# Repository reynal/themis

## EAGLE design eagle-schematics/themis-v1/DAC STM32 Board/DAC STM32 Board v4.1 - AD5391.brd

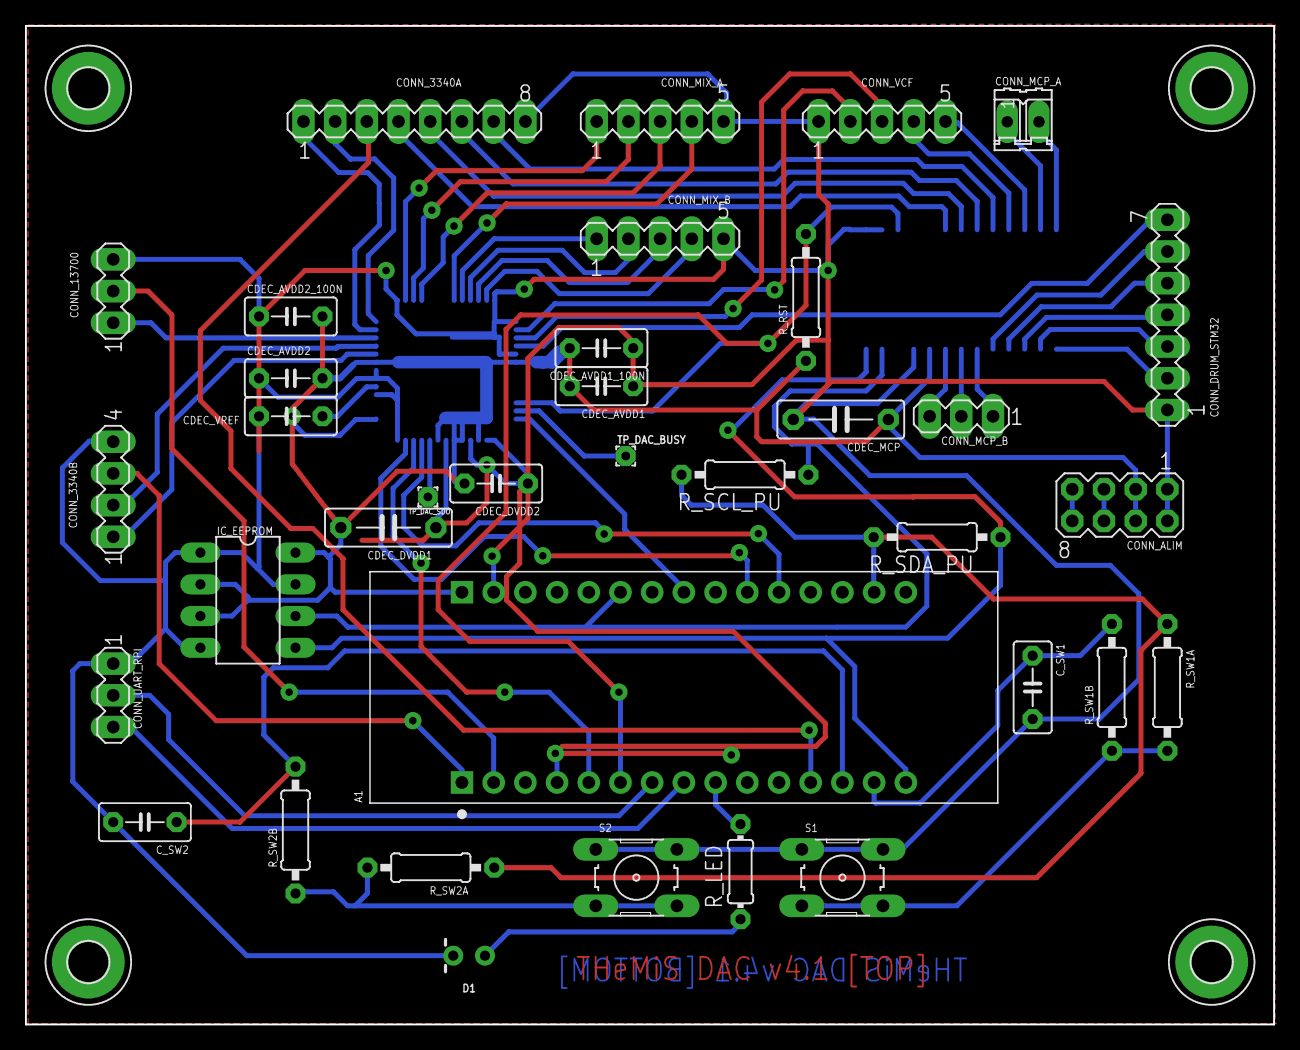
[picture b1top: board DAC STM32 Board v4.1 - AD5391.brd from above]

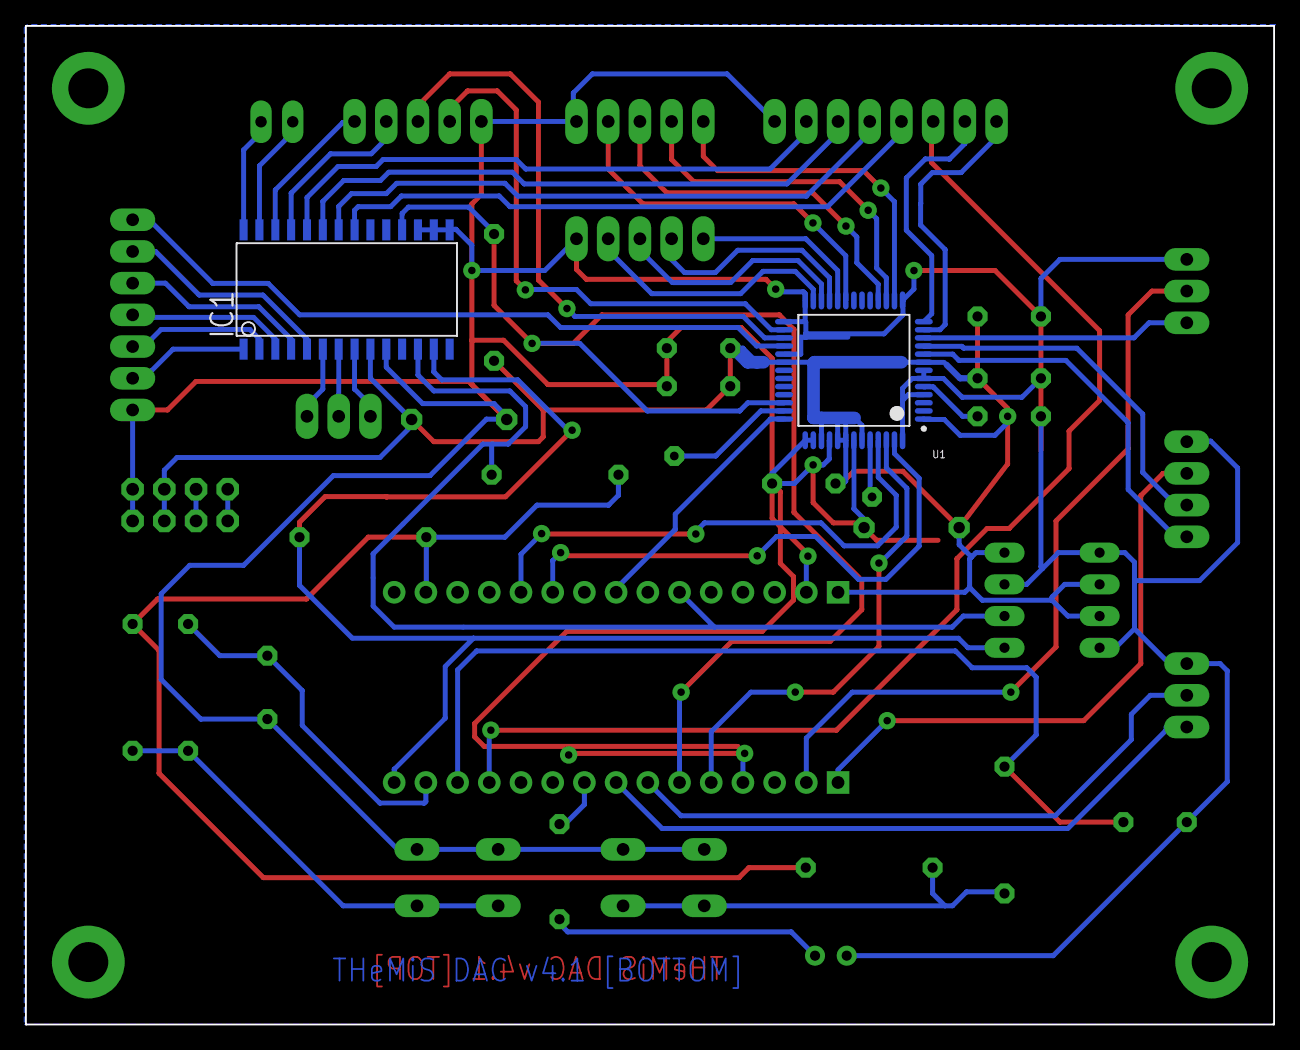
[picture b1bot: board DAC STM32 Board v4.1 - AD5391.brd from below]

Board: 2 copper layers, 100.0 x 80.0 mm, 42 parts (2 on the bottom side), 58 nets.

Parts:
A1: NUCLEO-F303K8; MODULE_NUCLEO-F303K8
CDEC_AVDD1, CDEC_AVDD2: 10u; C050-030X075
CDEC_AVDD1_100N, CDEC_AVDD2_100N: 100n; C050-030X075
CDEC_DVDD1: 100n; C075-032X103
CDEC_DVDD2: 100n; C050-030X075
CDEC_MCP: 100n; C075-032X103
CDEC_VREF: 100n; C050-030X075
CONN_3340A: MA08-1
CONN_3340B: MA04-1
CONN_13700: MA03-1
CONN_ALIM: MA04-2
CONN_DRUM_STM32: MA07-1
CONN_MCP_A: 02P
CONN_MCP_B: MA03-1
CONN_MIX_A: MA05-1
CONN_MIX_B: MA05-1
CONN_UART_RPI: MA03-1
CONN_VCF: MA05-1
C_SW1, C_SW2: 100n; C050-030X075
D1: LED_3MM-NS
H1, H2, H3, H4: MOUNT-PAD-ROUND3.2; 3,2-PAD
IC1: MCP23017SO; SO28W
IC_EEPROM: 24C04AP; DIL8
R_LED: 330; 0204/7
R_RST: 10k; 0207/10
R_SCL_PU: 1k; 0207/10
R_SDA_PU: 1k; 0207/10
R_SW1A, R_SW1B, R_SW2A, R_SW2B: 10k; 0207/10
S1, S2: B3F-10XX
TP_DAC_BUSY: PAD-TESTPOINT; 1,6/0,8
TP_DAC_SDO: PAD-TESTPOINT; 1,6/0,8
U1: ANALOG_DEVICES_AD5391BSTZ-3ANALOG_DEVICES_AD5391B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; ANALOG_DEVICES_AD5391BSTZ-3_0

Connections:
3V3: A1.4.14, R_SCL_PU.2, R_SDA_PU.2, R_SW1A.1, R_SW2A.1
5V: A1.4.1, CDEC_AVDD1.2, CDEC_AVDD1_100N.2, CDEC_AVDD2.2, CDEC_AVDD2_100N.2, CDEC_DVDD1.2, CDEC_DVDD2.2, CDEC_MCP.1, CONN_ALIM.3, CONN_ALIM.4, IC1.9, IC_EEPROM.2, IC_EEPROM.3, IC_EEPROM.8, R_RST.1, U1.1, U1.8, U1.32, U1.42, U1.44, U1.45, U1.47
15V: CONN_ALIM.7, CONN_ALIM.8
411_IN_PULSE: CONN_3340A.4, IC1.21
411_IN_SAW: CONN_3340A.7, IC1.24
411_IN_SYNC: CONN_3340A.6, IC1.23
411_IN_TRI: CONN_3340A.5, IC1.22
-15V: CONN_ALIM.5, CONN_ALIM.6
CALIB_3340A: A1.3.12, CONN_3340A.3
CALIB_3340B: A1.3.1, CONN_3340B.3
CALIB_13700: A1.3.2, CONN_13700.2
CV_CUTOFF: CONN_VCF.2, U1.28
CV_FREQ_3340A: CONN_3340A.1, U1.12
CV_FREQ_3340B: CONN_3340B.1, U1.9
CV_FREQ_13700: CONN_13700.1, U1.11
CV_PWM_3340A: CONN_3340A.2, U1.13
CV_PWM_3340B: CONN_3340B.2, U1.10
CV_RES: CONN_VCF.3, U1.29
DAC_LDAC: A1.4.8, U1.39
DAC_SYNC: A1.4.10, U1.51
DRUM_BD: CONN_DRUM_STM32.2, IC1.1
DRUM_RIM: CONN_DRUM_STM32.4, IC1.3
DRUM_SNARE: CONN_DRUM_STM32.3, IC1.2
DRUM_TOM1: CONN_DRUM_STM32.5, IC1.4
DRUM_TOM2: CONN_DRUM_STM32.6, IC1.5
GAIN1_A: CONN_MIX_A.3, U1.17
GAIN1_B: CONN_MIX_B.3, U1.24
GAIN2_A: CONN_MIX_A.4, U1.21
GAIN2_B: CONN_MIX_B.4, U1.25
GAIN3_A: CONN_MIX_A.1, U1.15
GAIN3_B: CONN_MIX_B.1, U1.22
GAIN4_A: CONN_MIX_A.2, U1.16
GAIN4_B: CONN_MIX_B.2, U1.23
GND: A1.3.4, A1.4.2, CDEC_AVDD1.1, CDEC_AVDD1_100N.1, CDEC_AVDD2.1, CDEC_AVDD2_100N.1, CDEC_DVDD1.1, CDEC_DVDD2.1, CDEC_MCP.2, CDEC_VREF.2, CONN_3340A.8, CONN_3340B.4, CONN_13700.3, CONN_ALIM.1, CONN_ALIM.2, CONN_DRUM_STM32.1, CONN_MIX_A.5, CONN_MIX_B.5, CONN_UART_RPI.1, CONN_VCF.1, C_SW1.2, C_SW2.2, D1.K, IC1.10, IC1.15, IC1.16, IC1.17, IC_EEPROM.1, IC_EEPROM.4, IC_EEPROM.7, S1.1, S1.2, S2.1, S2.2, U1.4, U1.6, U1.7, U1.14, U1.26, U1.27, U1.31, U1.40, U1.41, U1.43, U1.46, U1.52
GPB_5: CONN_MCP_B.1, IC1.6
GPB_6: CONN_MCP_B.2, IC1.7
GPB_7: CONN_MCP_B.3, IC1.8
IN_2NDORDER: CONN_VCF.4, IC1.25
IN_4THORDER: CONN_VCF.5, IC1.26
LED: A1.3.9, R_LED.2
unnamed: TP_DAC_BUSY.1, U1.38
unnamed: CONN_MCP_A.1, IC1.27
unnamed: D1.A, R_LED.1
unnamed: R_SW1A.2, R_SW1B.1, S1.3, S1.4
unnamed: CONN_MCP_A.2, IC1.28
unnamed: R_SW2A.2, R_SW2B.1, S2.3, S2.4
NOISE_GENE: CONN_DRUM_STM32.7, U1.30
REFOUT: CDEC_VREF.1, U1.5
RST: A1.3.6, IC1.18, R_RST.2, U1.37
SCL: A1.4.6, IC1.12, IC_EEPROM.6, R_SCL_PU.1
SDA: A1.3.15, IC1.13, IC_EEPROM.5, R_SDA_PU.1
SPI_CLK: A1.4.11, U1.49
SPI_MISO: TP_DAC_SDO.1, U1.48
SPI_MOSI: A1.3.5, U1.50
SW1: A1.3.14, C_SW1.1, R_SW1B.2
SW2: A1.3.13, C_SW2.1, R_SW2B.2
USART_RX_RPI_TX: A1.3.7, CONN_UART_RPI.2
USART_TX_RPI_RX: A1.3.8, CONN_UART_RPI.3

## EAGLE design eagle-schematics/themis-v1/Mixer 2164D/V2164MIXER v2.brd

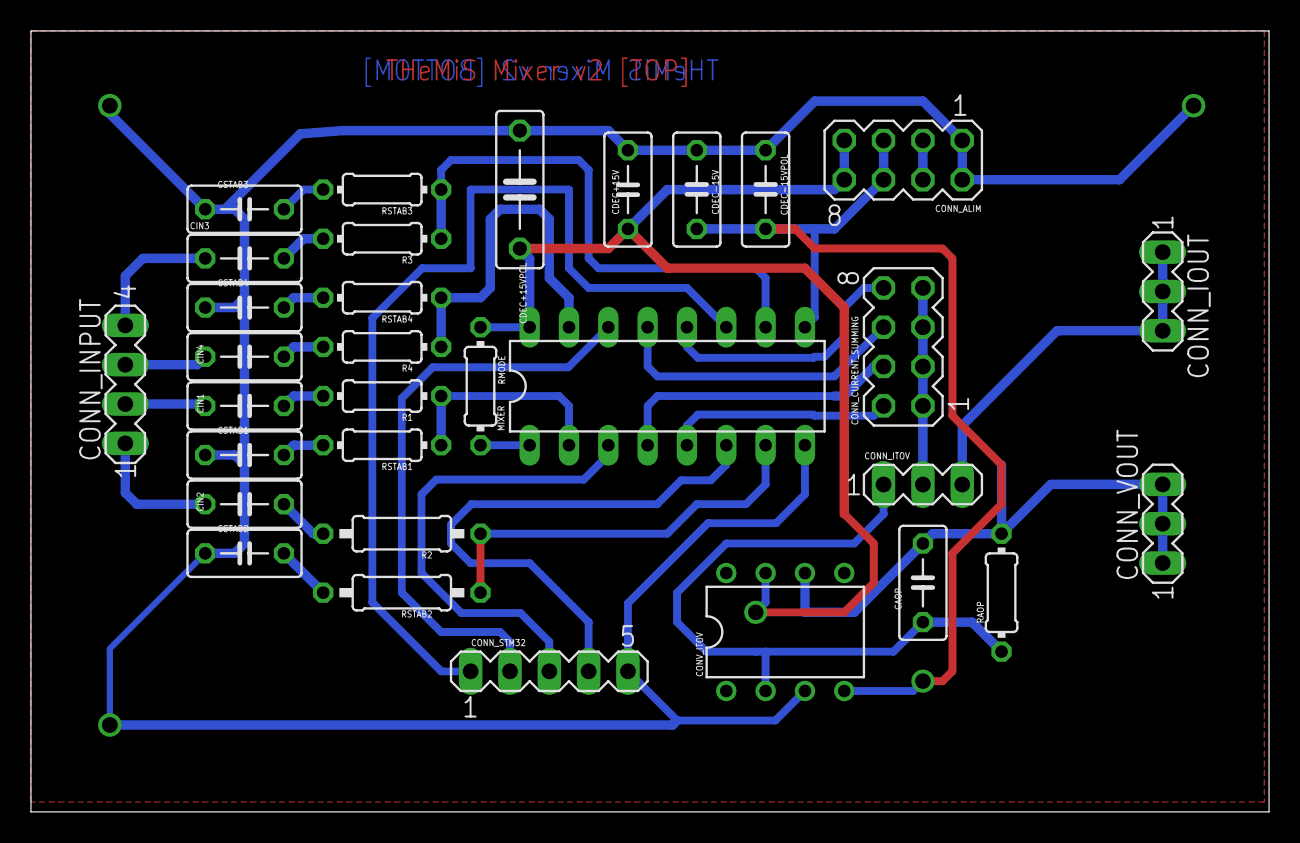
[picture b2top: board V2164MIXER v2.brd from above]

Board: 2 copper layers, 80.0 x 50.4 mm, 32 parts (0 on the bottom side), 33 nets.

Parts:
CAOP: 1p; C050-030X075
CDEC+15V: 100n; C050-030X075
CDEC+15VPOL: 100n; C075-032X103
CDEC-15V, CDEC-15VPOL: 100n; C050-030X075
CIN1, CIN2, CIN3, CIN4: 470n; C050-030X075
CONN_ALIM: MA04-2
CONN_CURRENT_SUMMING: MA04-2
CONN_INPUT: MA04-1
CONN_IOUT: MA03-1
CONN_ITOV: MA03-1
CONN_STM32: MA05-1
CONN_VOUT: MA03-1
CONV_ITOV: NE5534AN; DIL08
CSTAB1, CSTAB2, CSTAB3, CSTAB4: 560p; C050-030X075
MIXER: SSM2164_MULTI; DIL16
R1, R3, R4: 27k; 0204/7
R2: 27k; 0207/10
RAOP: 33K; 0204/7
RMODE: 8.2k; 0204/7
RSTAB1, RSTAB3, RSTAB4: 470; 0204/7
RSTAB2: 470; 0207/10

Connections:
2164_IN1: MIXER.2, R1.1, RSTAB1.1
2164_IN2: MIXER.7, R2.1, RSTAB2.1
2164_IN3: MIXER.10, R3.1, RSTAB3.1
2164_IN4: MIXER.15, R4.1, RSTAB4.1
2164_MODE: MIXER.1, RMODE.2
2164_OUT1: CONN_CURRENT_SUMMING.4, MIXER.4
2164_OUT2: CONN_CURRENT_SUMMING.2, MIXER.5
2164_OUT3: CONN_CURRENT_SUMMING.8, MIXER.12
2164_OUT4: CONN_CURRENT_SUMMING.6, MIXER.13
+5V: CONN_ALIM.3, CONN_ALIM.4
+15V: CDEC+15V.2, CDEC+15VPOL.2, CONN_ALIM.7, CONN_ALIM.8, CONV_ITOV.7, MIXER.16, RMODE.1
-15V: CDEC-15V.1, CDEC-15VPOL.1, CONN_ALIM.5, CONN_ALIM.6, CONV_ITOV.4, MIXER.9
AGND: CDEC+15V.1, CDEC+15VPOL.1, CDEC-15V.2, CDEC-15VPOL.2, CONN_ALIM.1, CONN_ALIM.2, CONN_STM32.5, CONV_ITOV.3, CSTAB1.1, CSTAB2.1, CSTAB3.1, CSTAB4.1, MIXER.8
CURRENT_OUT: CONN_IOUT.1, CONN_IOUT.2, CONN_IOUT.3, CONN_ITOV.3
GAIN1: CONN_STM32.3, MIXER.3
GAIN2: CONN_STM32.4, MIXER.6
GAIN3: CONN_STM32.1, MIXER.11
GAIN4: CONN_STM32.2, MIXER.14
IN1: CIN1.1, CONN_INPUT.2
IN2: CIN2.1, CONN_INPUT.1
IN3: CIN3.1, CONN_INPUT.4
IN4: CIN4.1, CONN_INPUT.3
MIXER_OUT: CONN_CURRENT_SUMMING.1, CONN_CURRENT_SUMMING.3, CONN_CURRENT_SUMMING.5, CONN_CURRENT_SUMMING.7, CONN_ITOV.2
unnamed: CIN4.2, R4.2
unnamed: CSTAB4.2, RSTAB4.2
unnamed: CIN2.2, R2.2
unnamed: CAOP.1, CONN_ITOV.1, CONV_ITOV.2, RAOP.1
unnamed: CSTAB2.2, RSTAB2.2
unnamed: CSTAB1.2, RSTAB1.2
unnamed: CIN1.2, R1.2
unnamed: CSTAB3.2, RSTAB3.2
unnamed: CIN3.2, R3.2
VOLTAGE_OUT: CAOP.2, CONN_VOUT.1, CONN_VOUT.2, CONN_VOUT.3, CONV_ITOV.6, RAOP.2

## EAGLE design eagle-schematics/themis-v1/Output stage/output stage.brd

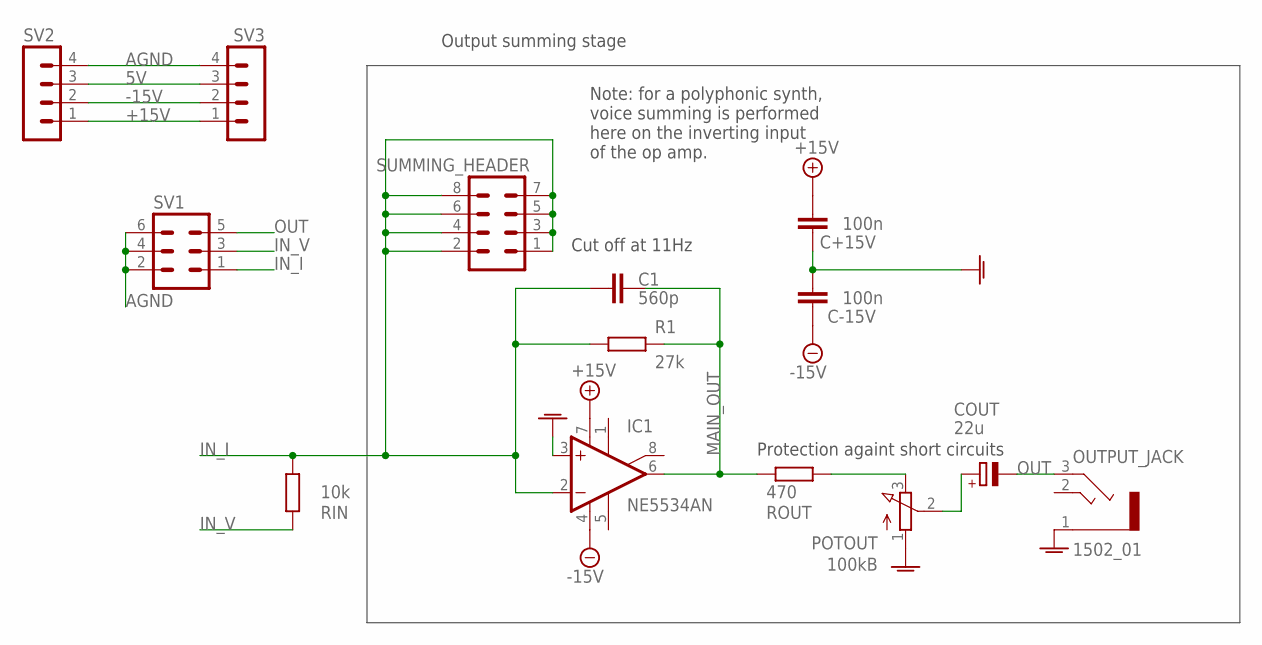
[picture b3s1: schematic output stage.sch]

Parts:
C1: 560p; C075-032X103
C+15V: 100n; C075-032X103
C-15V: 100n; C075-032X103
COUT: 22u; B45181A
IC1: NE5534AN; DIL08
OUTPUT_JACK: 1502_01
POTOUT: 100kB; 3RP/1610N
R1: 27k; 0207/10
RIN: 10k; 0207/10
ROUT: 470; 0207/12
SUMMING_HEADER: MA04-2
SV1: MA03-2
SV2, SV3: MA04-1

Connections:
5V: SV2.3, SV3.3
+15V: C+15V.2, IC1.7 (V+), SV2.1, SV3.1
-15V: C-15V.1, IC1.4 (V-), SV2.2, SV3.2
AGND: C+15V.1, C-15V.2, IC1.3 (+IN), OUTPUT_JACK.1, POTOUT.1 (A), SV1.2, SV1.4, SV1.6, SV2.4, SV3.4
IN_I: C1.2, IC1.2 (-IN), R1.2, RIN.1, SUMMING_HEADER.1, SUMMING_HEADER.2, SUMMING_HEADER.3, SUMMING_HEADER.4, SUMMING_HEADER.5, SUMMING_HEADER.6, SUMMING_HEADER.7, SUMMING_HEADER.8, SV1.1
IN_V: RIN.2, SV1.3
MAIN_OUT: C1.1, IC1.6 (OUT), R1.1, ROUT.2
unnamed: COUT.+, POTOUT.2 (S)
unnamed: POTOUT.3 (E), ROUT.1
OUT: COUT.-, OUTPUT_JACK.3 (2), SV1.5

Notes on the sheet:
Note: for a polyphonic synth, voice summing is performed here on the inverting input of the op amp.
Output summing stage
Cut off at 11Hz
Protection againt short circuits

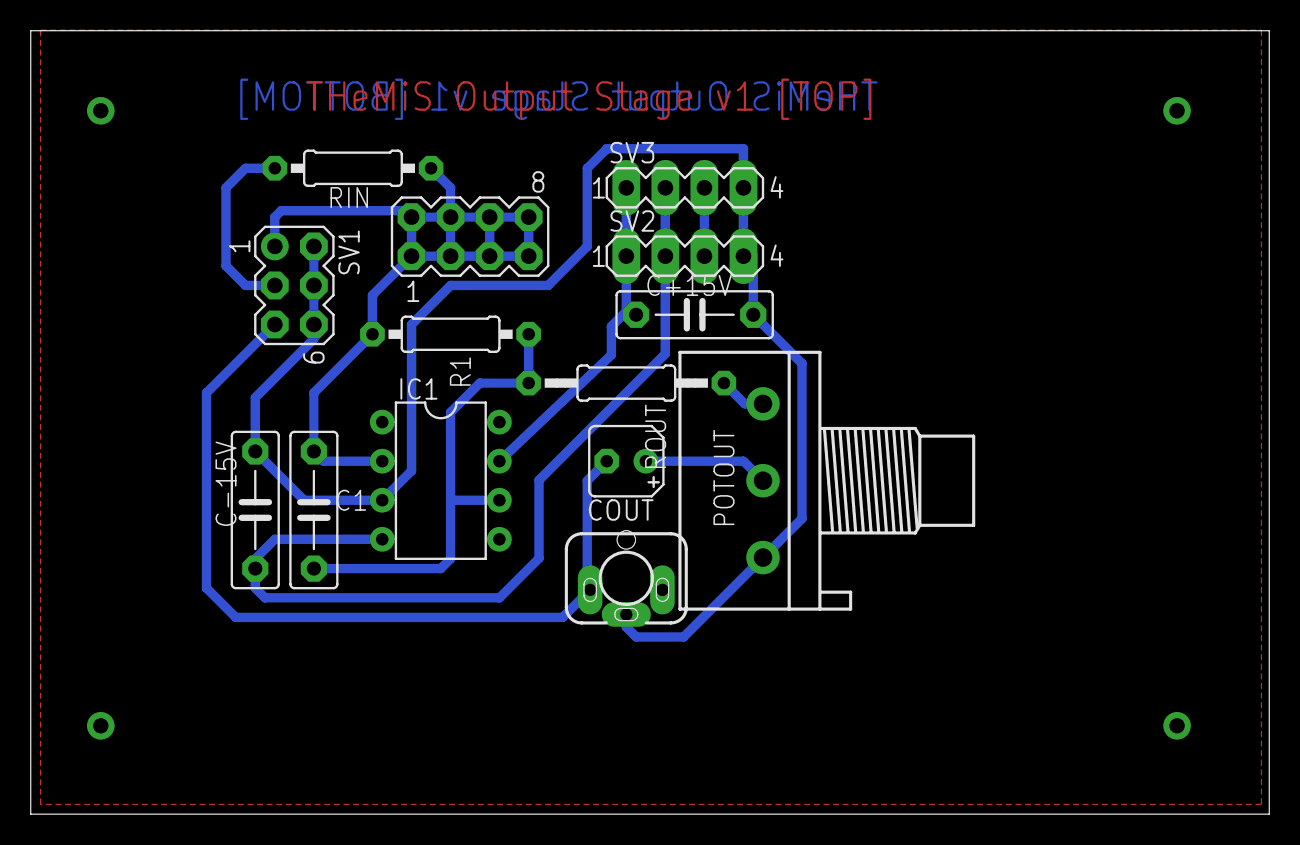
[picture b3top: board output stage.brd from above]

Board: 2 copper layers, 80.6 x 50.9 mm, 14 parts (0 on the bottom side), 10 nets.

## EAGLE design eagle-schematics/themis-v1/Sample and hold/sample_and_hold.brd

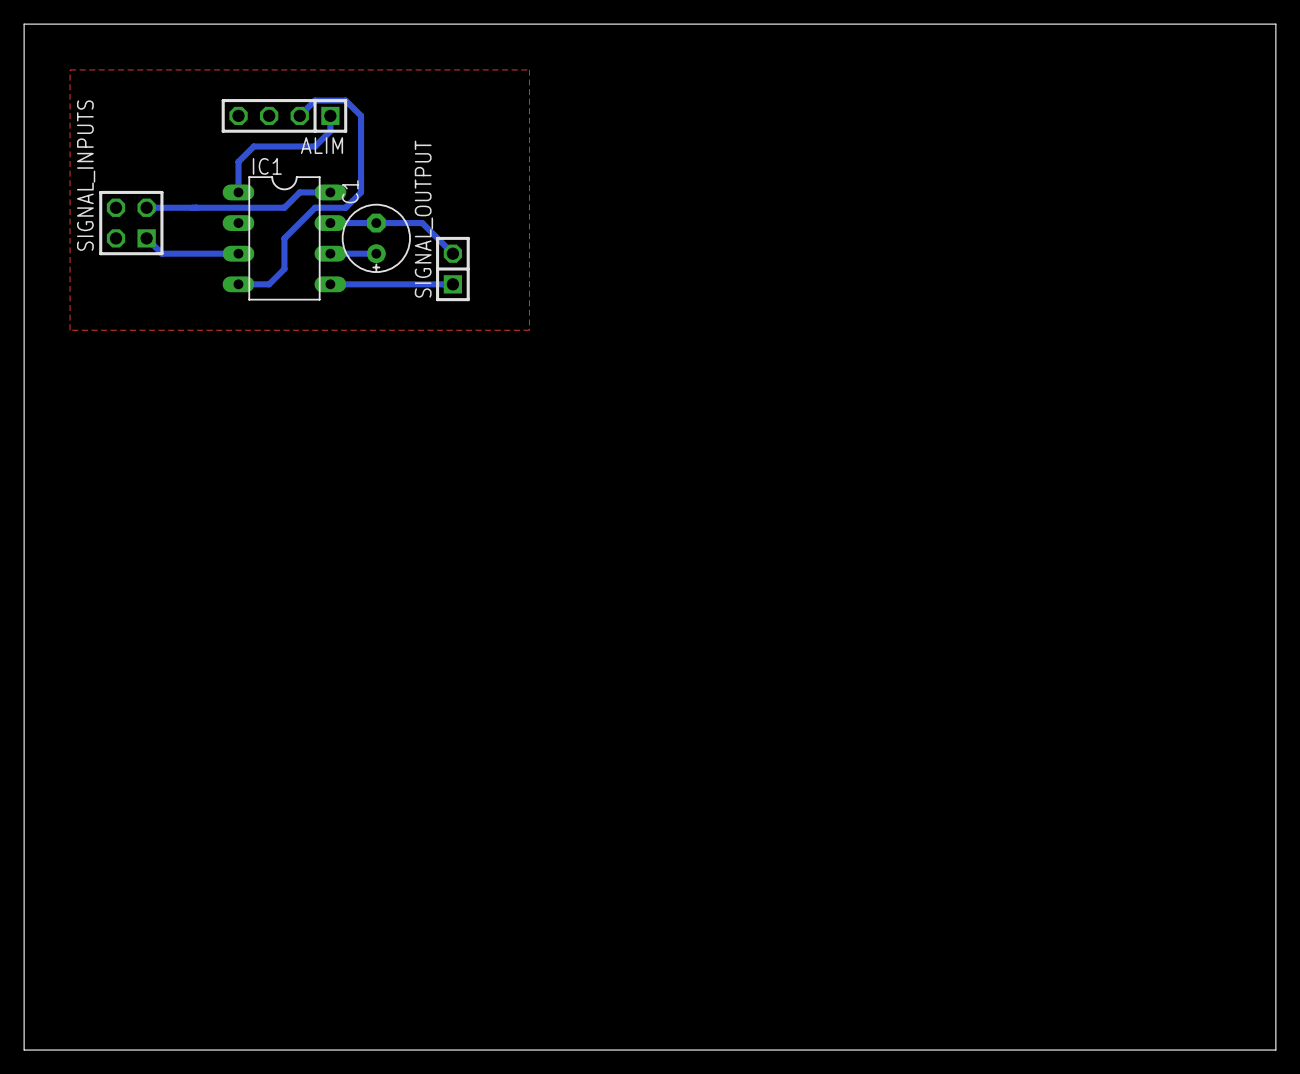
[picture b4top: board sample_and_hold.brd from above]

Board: 2 copper layers, 103.8 x 85.1 mm, 5 parts (0 on the bottom side), 7 nets.

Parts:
ALIM: 1X04
C1: E2,5-6E
IC1: TL081P; DIL08
SIGNAL_INPUTS: 2X02
SIGNAL_OUTPUT: 1X02

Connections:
+15V: ALIM.1, IC1.1
-15V: ALIM.2, IC1.4
AGND: ALIM.4, C1.-, IC1.7, SIGNAL_INPUTS.2, SIGNAL_INPUTS.4, SIGNAL_OUTPUT.2
IN: IC1.3, SIGNAL_INPUTS.1
LOGIC_INPUT: IC1.8, SIGNAL_INPUTS.3
unnamed: C1.+, IC1.6
OUT: IC1.5, SIGNAL_OUTPUT.1

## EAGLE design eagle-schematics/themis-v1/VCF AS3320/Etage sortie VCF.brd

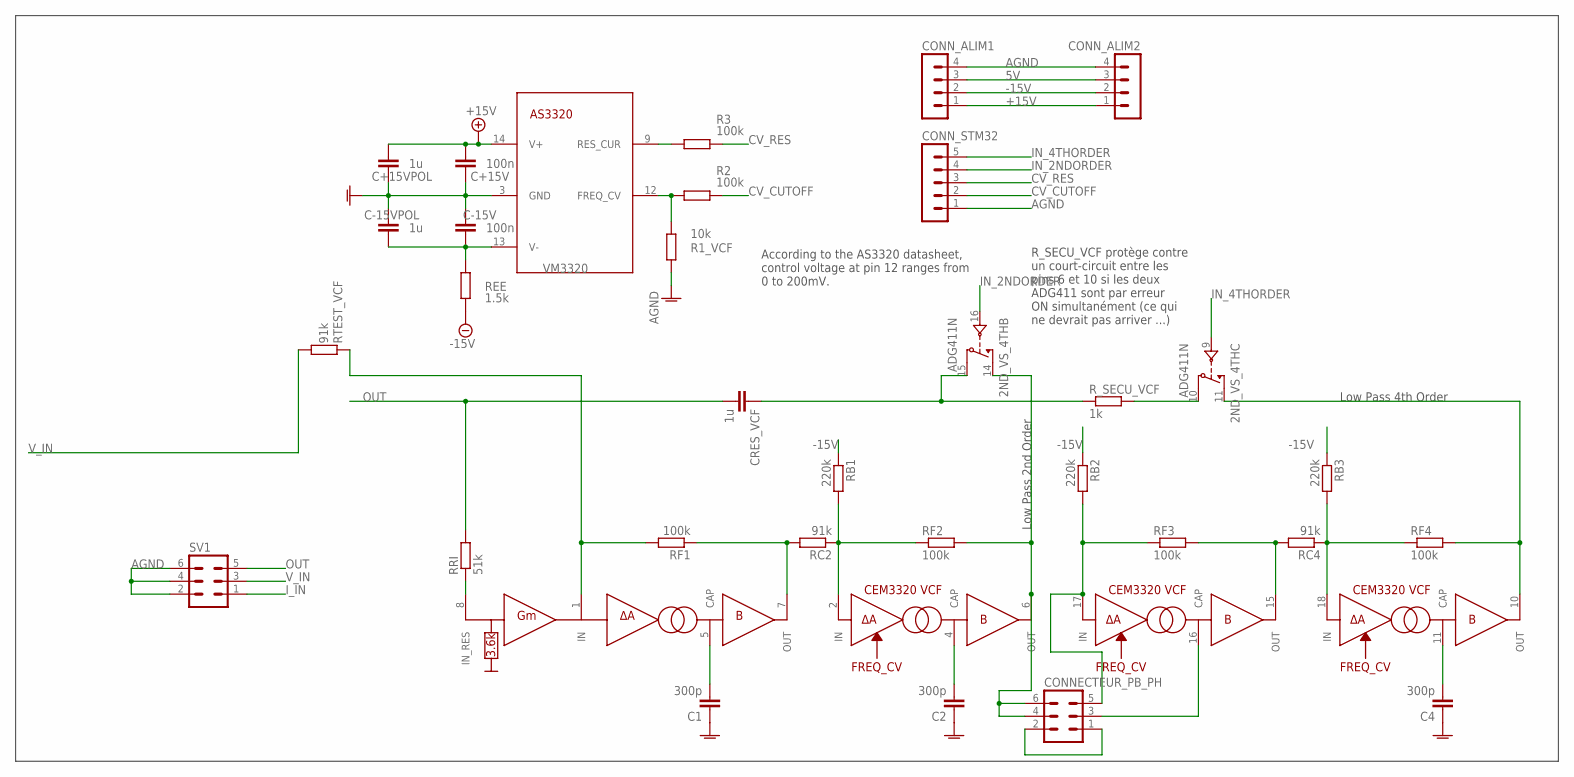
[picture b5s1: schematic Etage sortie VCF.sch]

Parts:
2ND_VS_4TH: ADG411N; DIL16
C1, C2, C4: 300p; C075-032X103
C+15V: 100n; C075-032X103
C+15VPOL: 1u; C075-032X103
C-15V: 100n; C075-032X103
C-15VPOL: 1u; C075-032X103
CONNECTEUR_PB_PH: MA03-2
CONN_ALIM1, CONN_ALIM2: MA04-1
CONN_STM32: MA05-1
CRES_VCF: 1u; C075-032X103
R1_VCF: 10k; 0204/7
R2, R3: 100k; 0204/7
RB1: 220k; 0207/10
RB2, RB3: 220k; 0204/7
RC2, RC4: 91k; 0204/7
REE: 1.5k; 0207/10
RF1, RF3: 100k; 0207/10
RF2, RF4: 100k; 0204/7
RRI: 51k; 0207/10
RTEST_VCF: 91k; 0207/10
R_SECU_VCF: 1k; 0204/7
SV1: MA03-2
VCF: AS3320; DIL18

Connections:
5V: CONN_ALIM1.3, CONN_ALIM2.3
+15V: C+15V.2, C+15VPOL.2, CONN_ALIM1.1, CONN_ALIM2.1, VCF.14 (V+)
-15V: CONN_ALIM1.2, CONN_ALIM2.2, RB1.1, RB2.1, RB3.1, REE.1
AGND: C1.1, C2.1, C4.1, C+15V.1, C+15VPOL.1, C-15V.2, C-15VPOL.2, CONN_ALIM1.4, CONN_ALIM2.4, CONN_STM32.1, R1_VCF.2, SV1.2, SV1.4, SV1.6, VCF.3 (GND)
CV_CUTOFF: CONN_STM32.2, R2.2
CV_RES: CONN_STM32.3, R3.2
GND: 2ND_VS_4TH.5 (GND)
IN_2NDORDER: 2ND_VS_4TH.16 (IN), CONN_STM32.4
IN_4THORDER: 2ND_VS_4TH.9 (IN), CONN_STM32.5
I_IN: SV1.1
unnamed: CONNECTEUR_PB_PH.3, VCF.16 (CAP)
unnamed: CONNECTEUR_PB_PH.1, CONNECTEUR_PB_PH.2
unnamed: C1.2, VCF.5 (CAP)
unnamed: C2.2, VCF.4 (CAP)
unnamed: C4.2, VCF.11 (CAP)
unnamed: R1_VCF.1, R2.1, VCF.12 (FREQ_CV)
unnamed: RC2.2, RF1.1, VCF.7 (OUT)
unnamed: 2ND_VS_4TH.15 (D), CRES_VCF.1, R_SECU_VCF.1
unnamed: RB1.2, RC2.1, RF2.1, VCF.2 (IN)
unnamed: 2ND_VS_4TH.14 (S), CONNECTEUR_PB_PH.4, CONNECTEUR_PB_PH.6, RF2.2, VCF.6 (OUT)
unnamed: 2ND_VS_4TH.11 (S), RF4.2, VCF.10 (OUT)
unnamed: CONNECTEUR_PB_PH.5, RB2.2, RF3.1, VCF.17 (IN)
unnamed: 2ND_VS_4TH.10 (D), R_SECU_VCF.2
unnamed: RC4.2, RF3.2, VCF.15 (OUT)
unnamed: RB3.2, RC4.1, RF4.1, VCF.18 (IN)
unnamed: RRI.1, VCF.8 (IN_RES)
unnamed: R3.1, VCF.9 (RES_CUR)
OUT: CRES_VCF.2, RRI.2, SV1.5
VCF_IN: RF1.2, RTEST_VCF.2, VCF.1 (IN)
VDD: 2ND_VS_4TH.13 (VDD)
VL: 2ND_VS_4TH.12 (VL)
VM3320: C-15V.1, C-15VPOL.1, REE.2, VCF.13 (V-)
VSS: 2ND_VS_4TH.4 (VSS)
V_IN: RTEST_VCF.1, SV1.3

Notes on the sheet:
According to the AS3320 datasheet, control voltage at pin 12 ranges from 0 to 200mV.
R_SECU_VCF protège contre un court-circuit entre les pins 6 et 10 si les deux ADG411 sont par erreur ON simultanément (ce qui ne devrait pas arriver ...)
Low Pass 2nd Order
Low Pass 4th Order

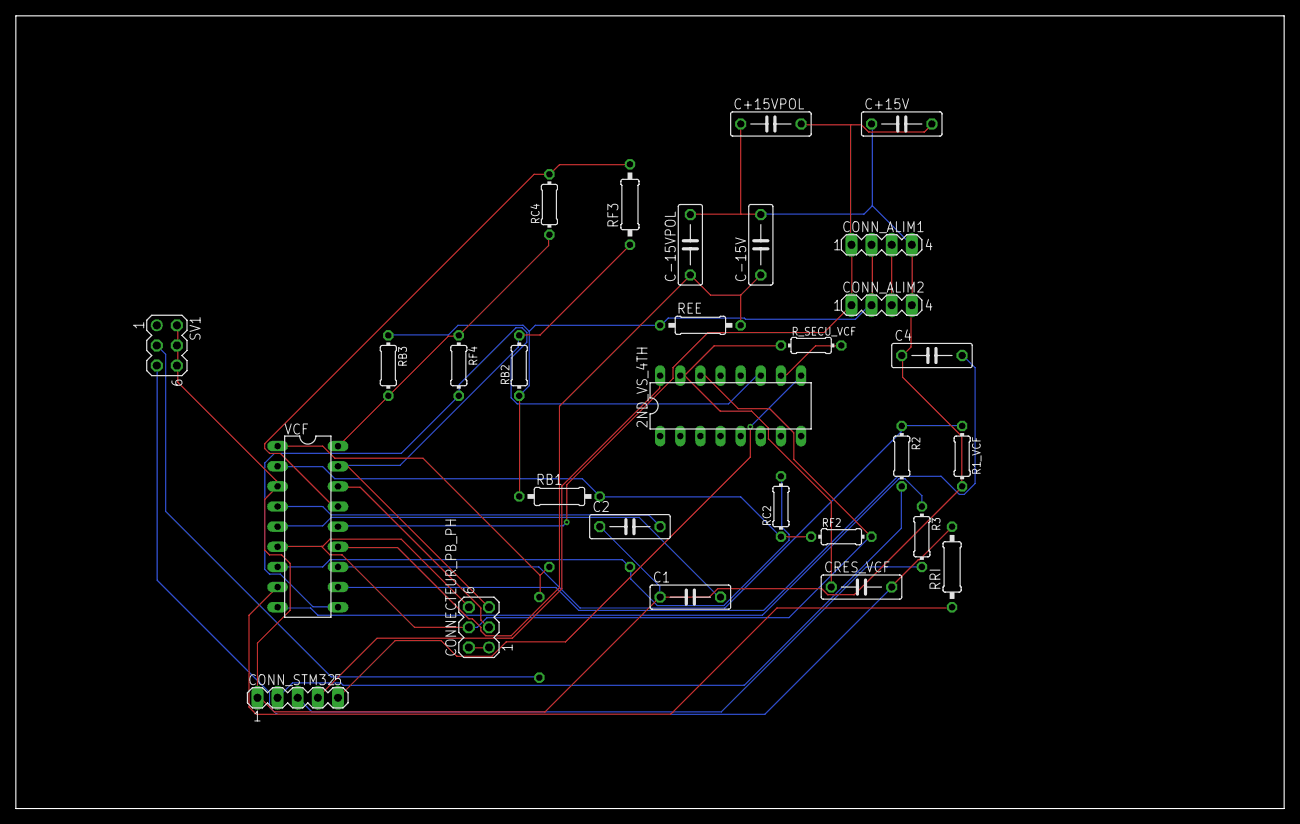
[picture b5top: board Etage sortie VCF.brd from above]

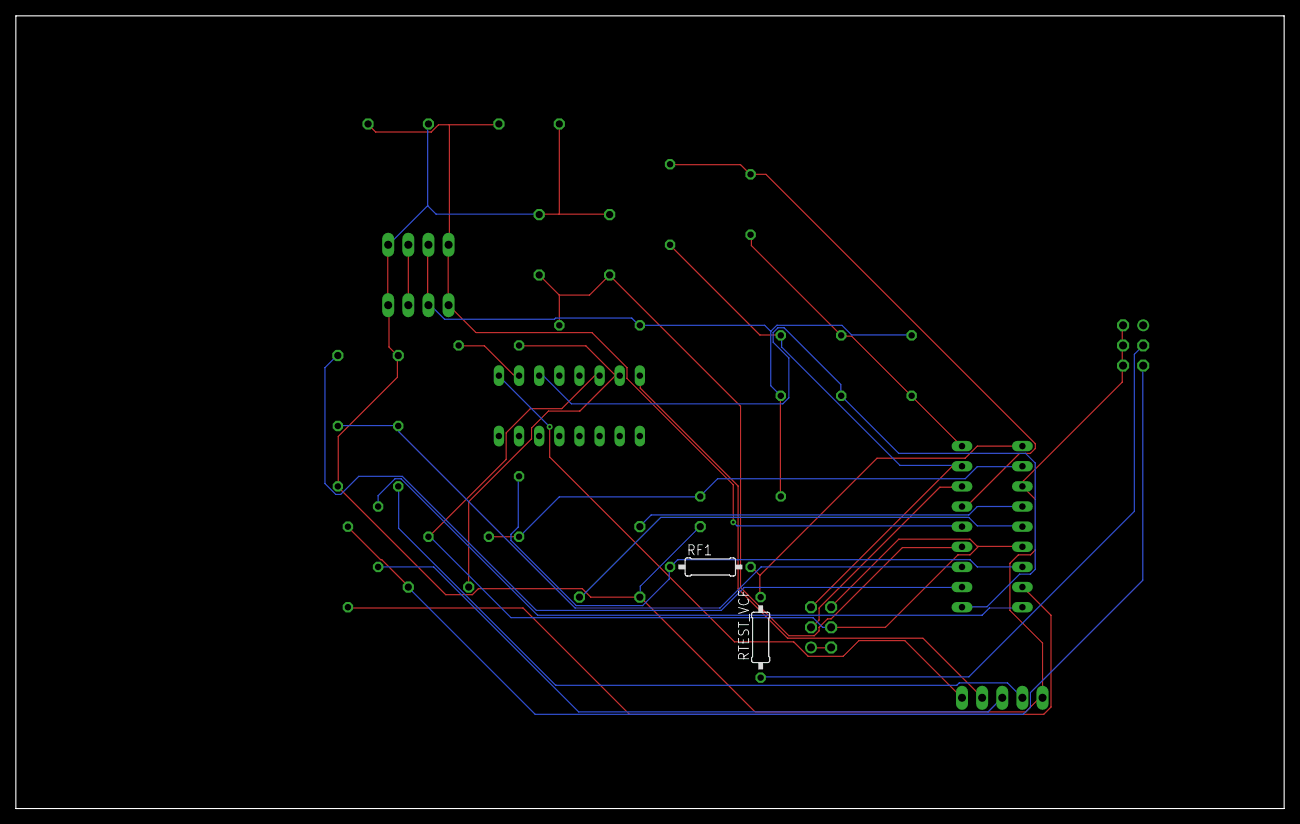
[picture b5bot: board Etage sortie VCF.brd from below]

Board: 2 copper layers, 160.0 x 100.0 mm, 31 parts (2 on the bottom side), 29 nets.

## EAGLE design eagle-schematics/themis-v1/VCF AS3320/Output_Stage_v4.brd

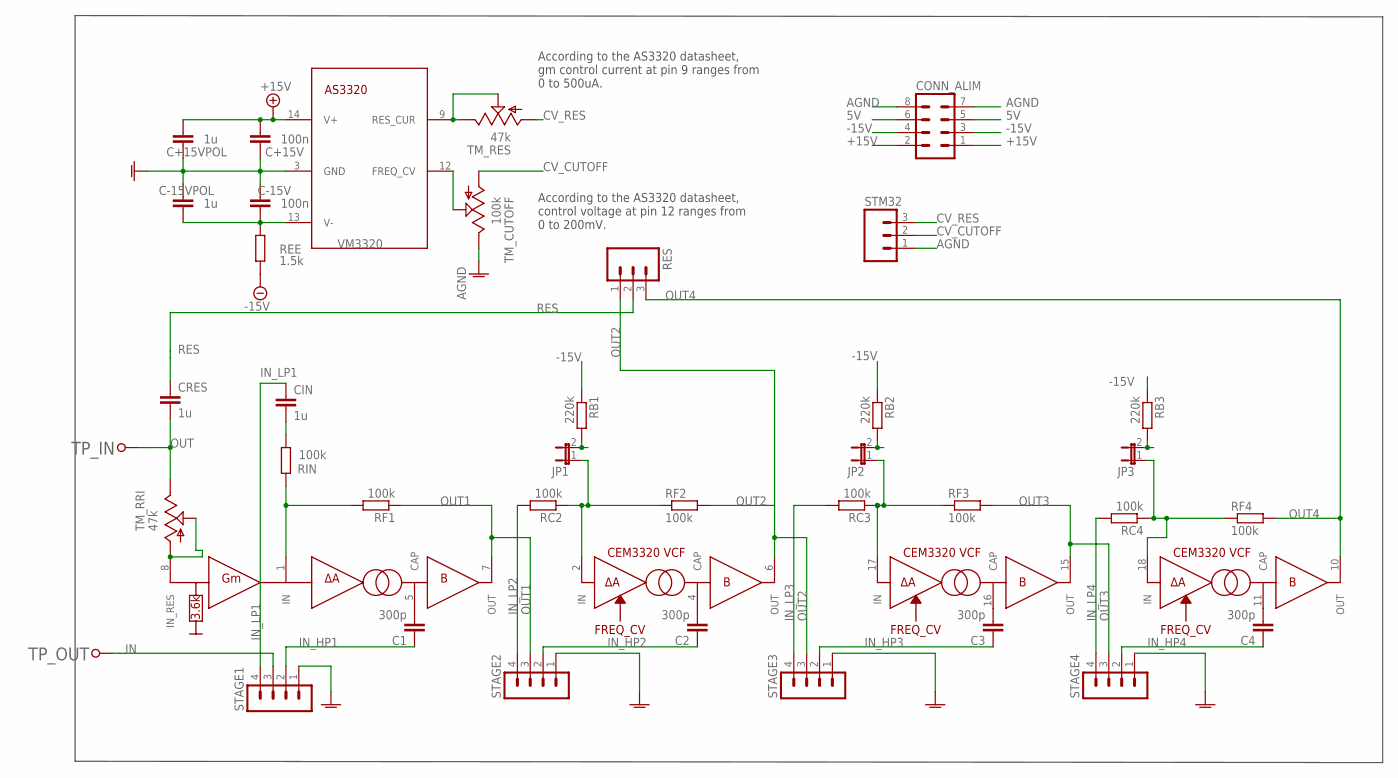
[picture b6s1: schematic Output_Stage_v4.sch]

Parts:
C1, C3, C4: 300p; C050-030X075
C2: 300p; C075-032X103
C+15V: 100n; C050-050X075
C+15VPOL: 1u; C050-050X075
C-15V: 100n; C050-050X075
C-15VPOL: 1u; C050-050X075
CIN: 1u; C050-030X075
CONN_ALIM: MA04-2
CRES: 1u; C050-030X075
JP1, JP2, JP3: JP1E; JP1
RB1, RB2, RB3: 220k; 0204/7
RC2, RC3, RC4: 100k; 0204/7
REE: 1.5k; 0207/7
RES: MA03; 03P
RF1, RF2, RF3, RF4: 100k; 0204/7
RIN: 100k; 0204/7
STAGE1, STAGE2, STAGE3, STAGE4: MA04-1
STM32: MA03; 03P
TM_CUTOFF: 100k; 6MM
TM_RES: 47k; 6MM
TM_RRI: 47k; 6MM
TP_IN: TESTPOINT; TESTPOINT_63
TP_OUT: TESTPOINT; TESTPOINT_63
VCF: AS3320; DIL18

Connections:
5V: CONN_ALIM.5, CONN_ALIM.6
+15V: C+15V.2, C+15VPOL.2, CONN_ALIM.1, CONN_ALIM.2, VCF.14 (V+)
-15V: CONN_ALIM.3, CONN_ALIM.4, RB1.1, RB2.1, RB3.1, REE.1
AGND: C+15V.1, C+15VPOL.1, C-15V.2, C-15VPOL.2, CONN_ALIM.7, CONN_ALIM.8, STAGE1.1, STAGE2.1, STAGE3.1, STAGE4.1, STM32.1, TM_CUTOFF.E, VCF.3 (GND)
CV_CUTOFF: STM32.2, TM_CUTOFF.A
CV_RES: STM32.3, TM_RES.A
IN: STAGE1.3, TP_OUT.P$1
IN_HP1: C1.1, STAGE1.2
IN_HP2: C2.1, STAGE2.2
IN_HP3: C3.1, STAGE3.2
IN_HP4: C4.1, STAGE4.2
IN_LP1: CIN.1, STAGE1.4
IN_LP2: RC2.2, STAGE2.4
IN_LP3: RC3.2, STAGE3.4
IN_LP4: RC4.2, STAGE4.4
unnamed: C3.2, VCF.16 (CAP)
unnamed: C1.2, VCF.5 (CAP)
unnamed: JP1.2, RB1.2
unnamed: JP2.2, RB2.2
unnamed: JP3.2, RB3.2
unnamed: JP3.1, RC4.1, RF4.1, VCF.18 (IN)
unnamed: CIN.2, RIN.1
unnamed: C2.2, VCF.4 (CAP)
unnamed: C4.2, VCF.11 (CAP)
unnamed: TM_CUTOFF.S, VCF.12 (FREQ_CV)
unnamed: JP1.1, RC2.1, RF2.1, VCF.2 (IN)
unnamed: JP2.1, RC3.1, RF3.1, VCF.17 (IN)
unnamed: TM_RRI.A, TM_RRI.S, VCF.8 (IN_RES)
unnamed: TM_RES.E, TM_RES.S, VCF.9 (RES_CUR)
OUT: CRES.2, TM_RRI.E, TP_IN.P$1
OUT1: RF1.1, STAGE2.3, VCF.7 (OUT)
OUT2: RES.1, RF2.2, STAGE3.3, VCF.6 (OUT)
OUT3: RF3.2, STAGE4.3, VCF.15 (OUT)
OUT4: RES.3, RF4.2, VCF.10 (OUT)
RES: CRES.1, RES.2
VCF_IN: RF1.2, RIN.2, VCF.1 (IN)
VM3320: C-15V.1, C-15VPOL.1, REE.2, VCF.13 (V-)

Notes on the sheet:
According to the AS3320 datasheet, control voltage at pin 12 ranges from 0 to 200mV.
According to the AS3320 datasheet, gm control current at pin 9 ranges from 0 to 500uA.

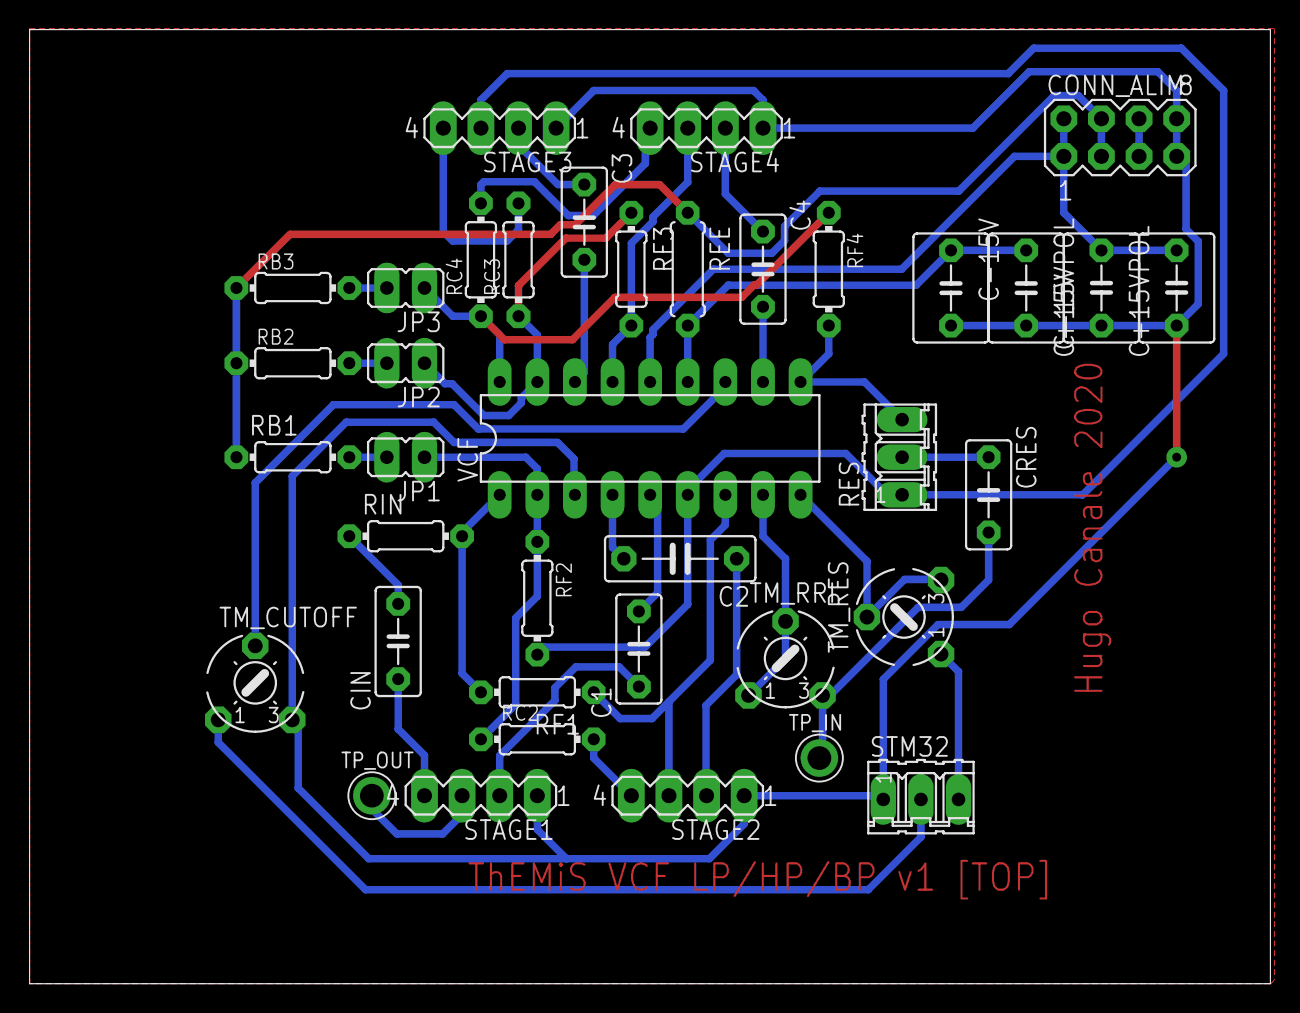
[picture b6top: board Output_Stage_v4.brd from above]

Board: 2 copper layers, 83.8 x 64.4 mm, 38 parts (0 on the bottom side), 37 nets.

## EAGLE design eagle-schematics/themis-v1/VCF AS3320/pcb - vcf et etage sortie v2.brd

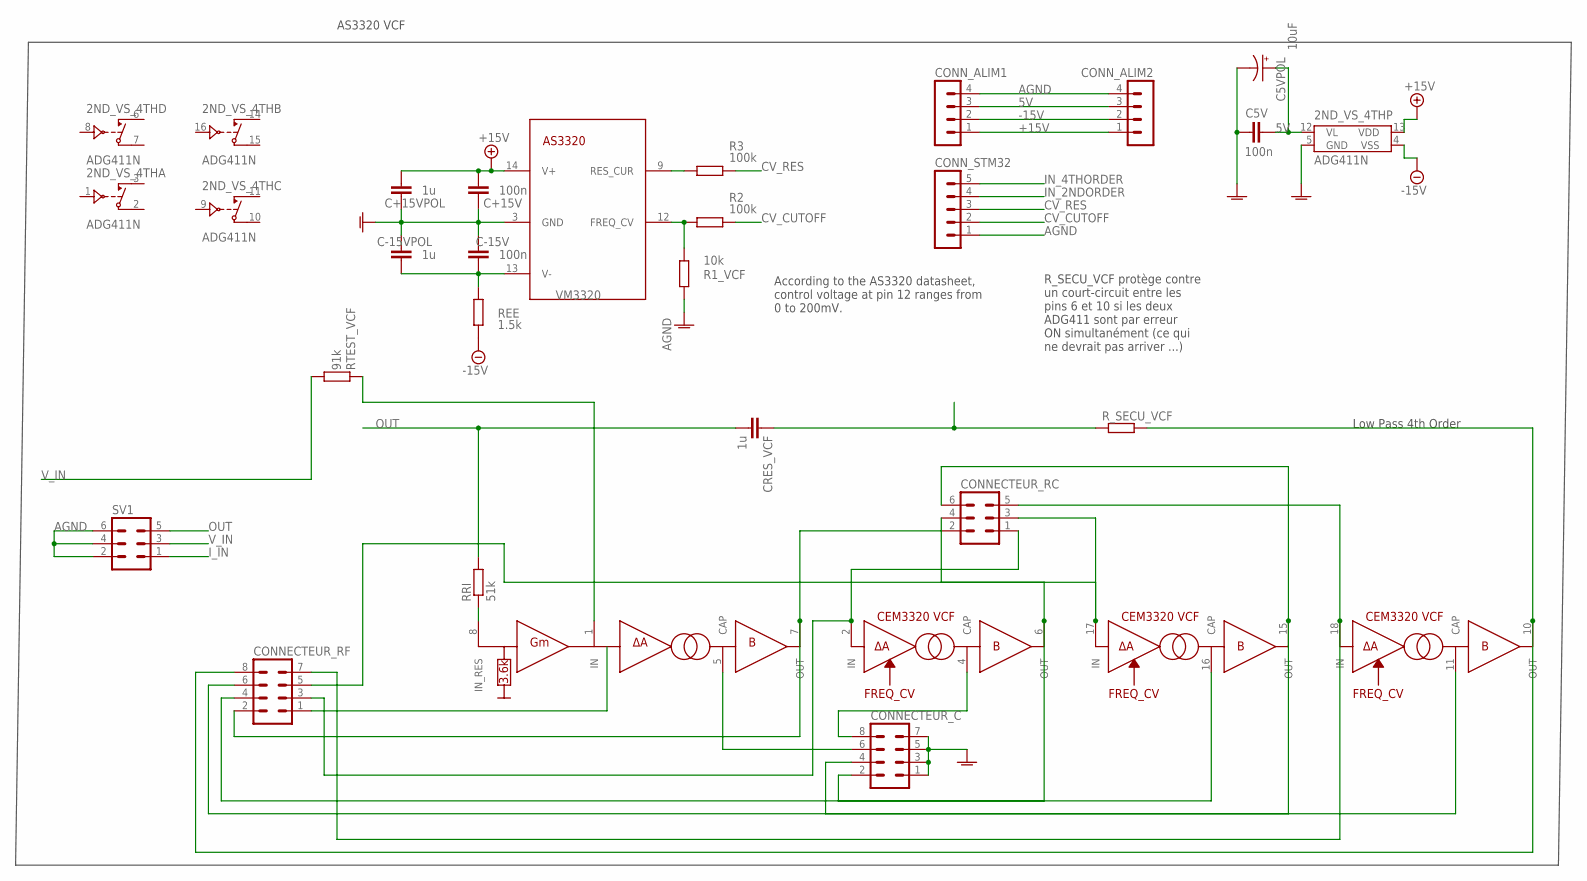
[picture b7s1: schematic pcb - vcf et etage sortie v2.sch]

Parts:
2ND_VS_4TH: ADG411N; DIL16
C5V: 100n; C050-024X044
C5VPOL: 10uF; CPOL-RADIAL-2.5MM-5MM-KIT
C+15V: 100n; C050-024X044
C+15VPOL: 1u; C050-024X044
C-15V: 100n; C050-025X075
C-15VPOL: 1u; C075-032X103
CONNECTEUR_C: MA04-2
CONNECTEUR_RC: MA03-2
CONNECTEUR_RF: MA04-2
CONN_ALIM1, CONN_ALIM2: MA04-1
CONN_STM32: MA05-1
CRES_VCF: 1u; C075-032X103
R1_VCF: 10k; 0204/7
R2: 100k; 0204/5
R3: 100k; 0204/7
REE: 1.5k; 0207/10
RRI: 51k; 0207/10
RTEST_VCF: 91k; 0204/5
R_SECU_VCF: 1k; 0204/7
SV1: MA03-2
VCF: AS3320; DIL18

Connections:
5V: 2ND_VS_4TH.12 (VL), C5V.1, C5VPOL.1 (+), CONN_ALIM1.3, CONN_ALIM2.3
+15V: 2ND_VS_4TH.13 (VDD), C+15V.2, C+15VPOL.2, CONN_ALIM1.1, CONN_ALIM2.1, VCF.14 (V+)
-15V: 2ND_VS_4TH.4 (VSS), CONN_ALIM1.2, CONN_ALIM2.2, REE.1
AGND: 2ND_VS_4TH.5 (GND), C5V.2, C5VPOL.2 (-), C+15V.1, C+15VPOL.1, C-15V.2, C-15VPOL.2, CONNECTEUR_C.1, CONNECTEUR_C.3, CONNECTEUR_C.5, CONNECTEUR_C.7, CONN_ALIM1.4, CONN_ALIM2.4, CONN_STM32.1, R1_VCF.2, SV1.2, SV1.4, SV1.6, VCF.3 (GND)
CV_CUTOFF: CONN_STM32.2, R2.2
CV_RES: CONN_STM32.3, R3.2
IN_2NDORDER: CONN_STM32.4
IN_4THORDER: CONN_STM32.5
I_IN: SV1.1
unnamed: CONNECTEUR_RC.2, CONNECTEUR_RF.2, VCF.7 (OUT)
unnamed: CONNECTEUR_C.4, VCF.11 (CAP)
unnamed: CONNECTEUR_C.2, VCF.16 (CAP)
unnamed: CONNECTEUR_C.8, VCF.4 (CAP)
unnamed: CONNECTEUR_C.6, VCF.5 (CAP)
unnamed: CONNECTEUR_RC.1, CONNECTEUR_RF.3, VCF.2 (IN)
unnamed: CONNECTEUR_RC.4, CONNECTEUR_RF.4, VCF.6 (OUT)
unnamed: CONNECTEUR_RC.3, CONNECTEUR_RF.5, VCF.17 (IN)
unnamed: CONNECTEUR_RC.6, CONNECTEUR_RF.6, VCF.15 (OUT)
unnamed: CONNECTEUR_RC.5, CONNECTEUR_RF.7, VCF.18 (IN)
unnamed: R1_VCF.1, R2.1, VCF.12 (FREQ_CV)
unnamed: CRES_VCF.1, R_SECU_VCF.1
unnamed: CONNECTEUR_RF.8, R_SECU_VCF.2, VCF.10 (OUT)
unnamed: RRI.1, VCF.8 (IN_RES)
unnamed: R3.1, VCF.9 (RES_CUR)
OUT: CRES_VCF.2, RRI.2, SV1.5
VCF_IN: RTEST_VCF.2, VCF.1 (IN)
VM3320: C-15V.1, C-15VPOL.1, REE.2, VCF.13 (V-)
V_IN: RTEST_VCF.1, SV1.3

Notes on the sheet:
According to the AS3320 datasheet, control voltage at pin 12 ranges from 0 to 200mV.
AS3320 VCF
R_SECU_VCF protège contre un court-circuit entre les pins 6 et 10 si les deux ADG411 sont par erreur ON simultanément (ce qui ne devrait pas arriver ...)
Low Pass 4th Order

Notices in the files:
parts and their libraries:
SparkFun-LED: Licensing: Creative Commons ShareAlike 4.0 International - https://creativecommons.org/licenses/by-sa/4.0
